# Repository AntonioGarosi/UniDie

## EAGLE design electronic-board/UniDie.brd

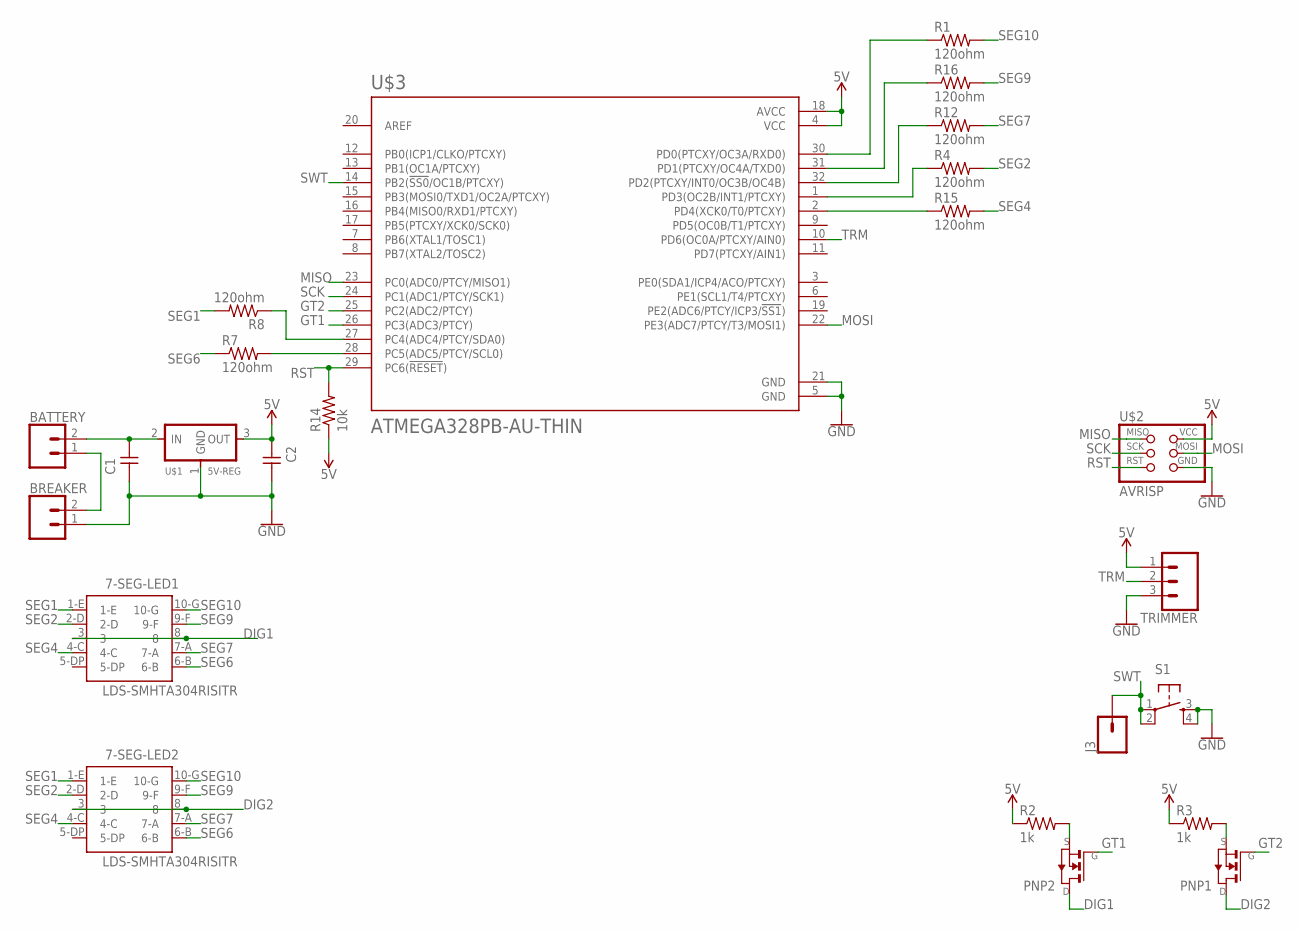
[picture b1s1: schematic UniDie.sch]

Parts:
7-SEG-LED1, 7-SEG-LED2: LDS-SMHTA304RISITR; 10-SMD
BATTERY: CONN_021X02_NO_SILK; 1X02_NO_SILK
BREAKER: CONN_021X02_NO_SILK; 1X02_NO_SILK
C1, C2: CAP-UNPOLARIZEDFAB; C1206FAB
J3: CONN_01PTH_NO_SILK_YES_STOP; 1X01_NO_SILK
PNP1, PNP2: NMOSFETSOT23; SOT-23
R1, R4, R7, R8, R12, R15, R16: 120ohm; R1206FAB
R2, R3: 1k; R1206FAB
R14: 10k; R1206FAB
S1: 6MM_SWITCH6MM_SWITCH; 6MM_SWITCH
TRIMMER: CONN_031X03_NO_SILK; 1X03_NO_SILK
U$1: 5V-REG; SOT-23
U$2: AVRISP; 2X03
U$3: ATMEGA328PB-AU-THIN; TQFP32-08THIN

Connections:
5V: C2.1, R2.1, R3.1, R14.1, TRIMMER.1, U$1.3 (OUT), U$2.2 (VCC), U$3.4 (VCC), U$3.18 (AVCC)
DIG1: 7-SEG-LED1.3, 7-SEG-LED1.8, PNP2.1 (D)
DIG2: 7-SEG-LED2.3, 7-SEG-LED2.8, PNP1.1 (D)
GND: BREAKER.1, C1.1, C2.2, S1.3 (S), S1.4 (S1), TRIMMER.3, U$1.1 (GND), U$2.6 (GND), U$3.5 (GND), U$3.21 (GND)
GT1: PNP2.3 (G), U$3.26 (PC3(ADC3/PTCY))
GT2: PNP1.3 (G), U$3.25 (PC2(ADC2/PTCY))
MISO: U$2.1 (MISO), U$3.23 (PC0(ADC0/PTCY/MISO1))
MOSI: U$2.4 (MOSI), U$3.22 (PE3(ADC7/PTCY/T3/MOSI1))
unnamed: BATTERY.2, C1.2, U$1.2 (IN)
unnamed: PNP1.2 (S), R3.2
unnamed: R7.2, U$3.28 (PC5(ADC5/PTCY/SCL0))
unnamed: R8.1, U$3.27 (PC4(ADC4/PTCY/SDA0))
unnamed: BATTERY.1, BREAKER.2
unnamed: R15.1, U$3.2 (PD4(XCK0/T0/PTCXY))
unnamed: R4.1, U$3.1 (PD3(OC2B/INT1/PTCXY))
unnamed: R12.1, U$3.32 (PD2(PTCXY/INT0/OC3B/OC4B))
unnamed: R16.1, U$3.31 (PD1(PTCXY/OC4A/TXD0))
unnamed: R1.1, U$3.30 (PD0(PTCXY/OC3A/RXD0))
unnamed: PNP2.2 (S), R2.2
RST: R14.2, U$2.5 (RST), U$3.29 (PC6(!RESET!))
SCK: U$2.3 (SCK), U$3.24 (PC1(ADC1/PTCY/SCK1))
SEG1: 7-SEG-LED1.1-E, 7-SEG-LED2.1-E, R8.2
SEG2: 7-SEG-LED1.2-D, 7-SEG-LED2.2-D, R4.2
SEG4: 7-SEG-LED1.4-C, 7-SEG-LED2.4-C, R15.2
SEG6: 7-SEG-LED1.6-B, 7-SEG-LED2.6-B, R7.1
SEG7: 7-SEG-LED1.7-A, 7-SEG-LED2.7-A, R12.2
SEG9: 7-SEG-LED1.9-F, 7-SEG-LED2.9-F, R16.2
SEG10: 7-SEG-LED1.10-G, 7-SEG-LED2.10-G, R1.2
SWT: J3.1, S1.1, S1.2 (P1), U$3.14 (PB2(!SS0!/OC1B/PTCXY))
TRM: TRIMMER.2, U$3.10 (PD6(OC0A/PTCXY/AIN0))

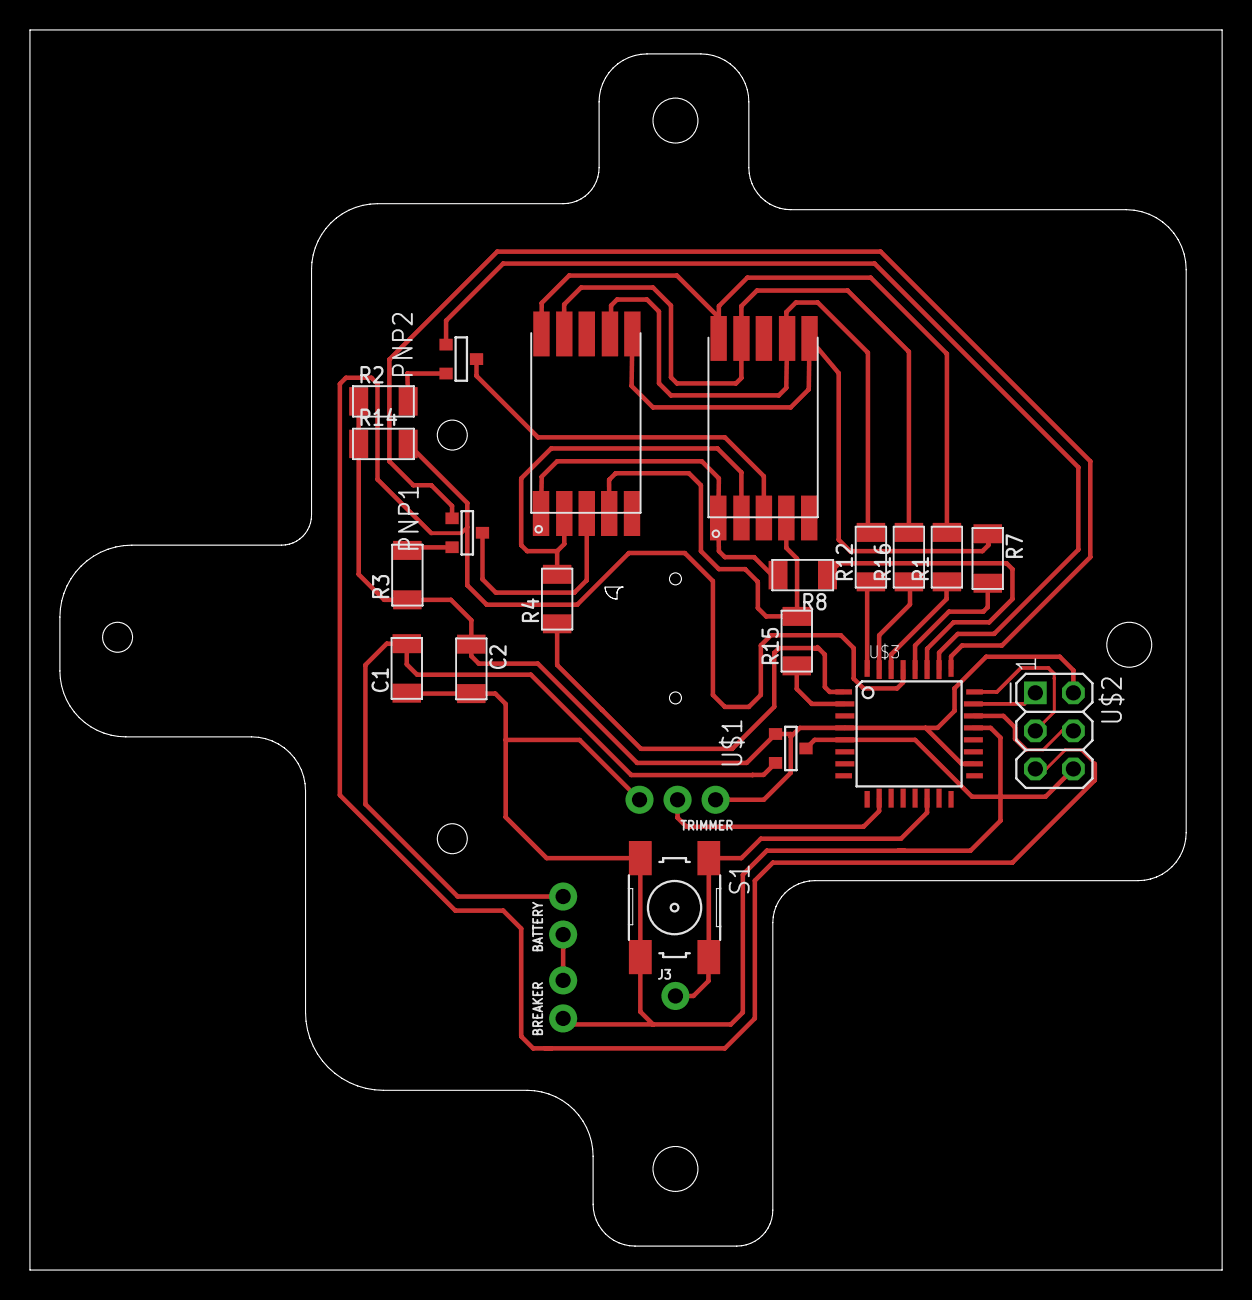
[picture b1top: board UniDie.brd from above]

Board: 2 copper layers, 79.6 x 82.8 mm, 24 parts (0 on the bottom side), 30 nets.

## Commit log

2018-11-07 Added .gitignore
2018-11-07 Fixed .gitignore
2018-11-15 Update on schematic and board.
2018-11-21 Finished schematic and approximate board layout. Updated electronics BOM
2018-11-23 Started adapting board layout to prouct requirements
2018-11-26 Updated board layout. Heavily optimized traces and components distribution
2018-12-02 Updated dxf layout on board. Removed dc plug and added power pins. Added holes to board
2018-12-06 Updated board design with potentiomenter layout and traces optimizations
2018-12-07 Added circuit breaker to board to switch on/off power
2018-12-12 Adapted parts and routes for milling. Prepared milling files
2019-02-09 Design schematics for new controller
2019-02-09 Add thinner traces package for the microcontroller, re-arrange routes. To be finishes
2019-02-09 Revert "Adapted parts and routes for milling. Prepared milling files"
    This reverts commit d229ee454f50b57581f4fd08392e80f763665f52.
2019-02-09 Find a board layout apt for 328pb
2019-02-09 Adjust all routes. Adjust trimmer holes. Adjust outline

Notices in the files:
parts and their libraries:
SparkFun-Connectors: Licensing: Creative Commons ShareAlike 4.0 International - https://creativecommons.org/licenses/by-sa/4.0
